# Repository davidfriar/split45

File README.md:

# The Split Forty Five

A small mechanical keyboard for those who cannot decide if they are ancient or modern.

* "Traditional" row-staggered layout
* Split for better ergonomics
* Based on the Nice!Nano controller for very low power consumption
* Uses Bluetooth Low Energy (BLE) both to connect each half and to connect to the computer

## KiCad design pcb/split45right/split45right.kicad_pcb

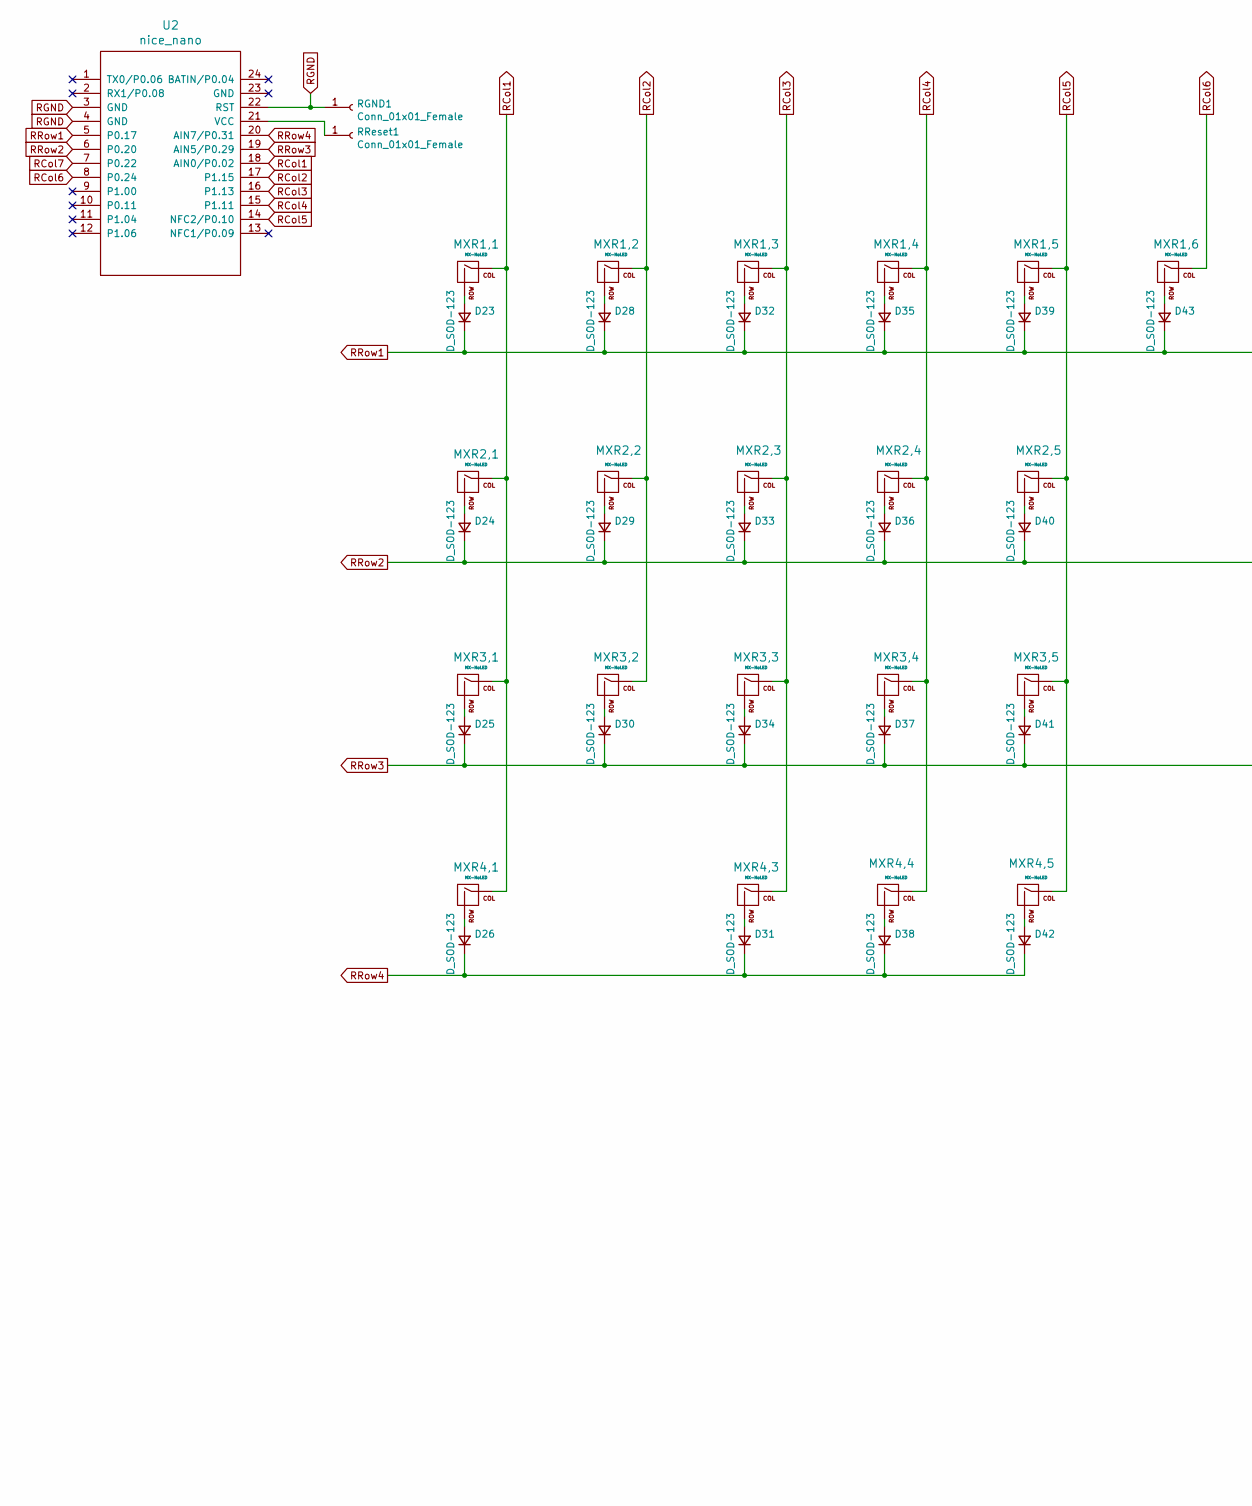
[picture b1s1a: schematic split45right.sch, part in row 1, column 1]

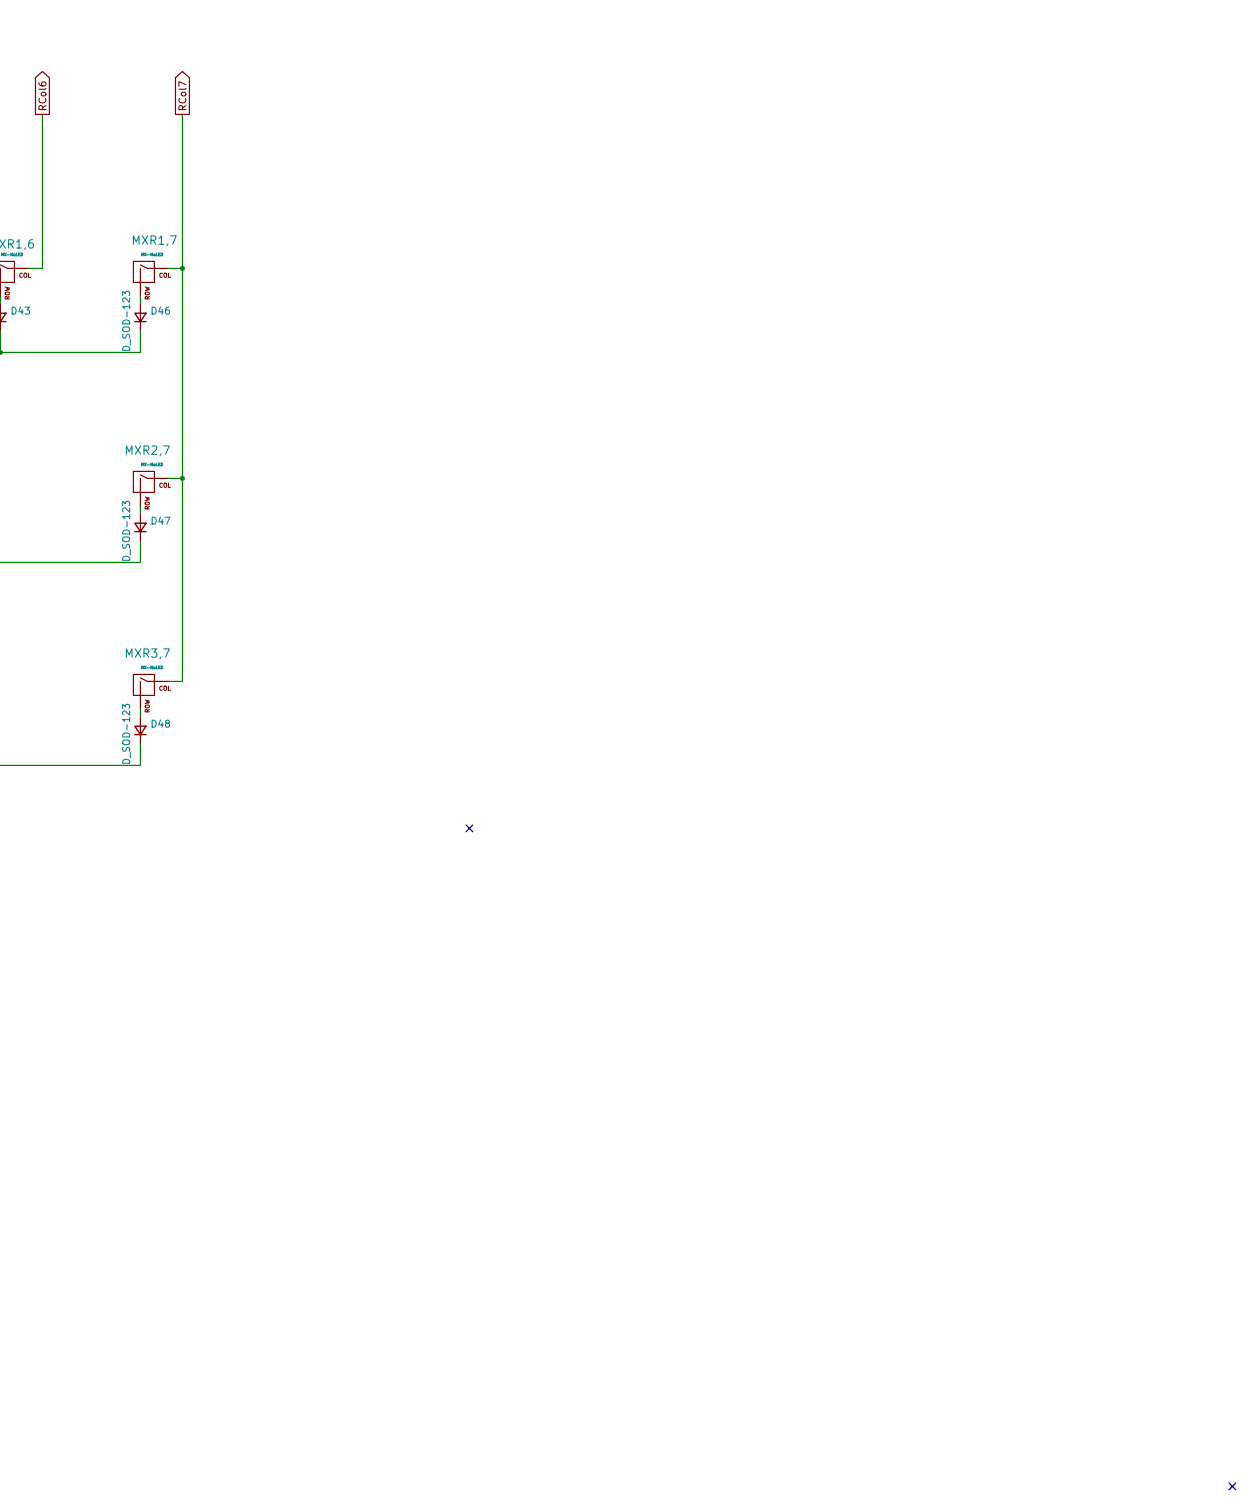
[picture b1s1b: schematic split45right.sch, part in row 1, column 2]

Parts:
D23, D24, D25, D26, D28, D29, D30, D31, D32, D33, D34, D35, D36, D37, D38, D39, D40, D41, D42, D43, D46, D47, D48: D_SOD-123
MXR1,1, MXR1,2, MXR1,3, MXR1,4, MXR1,5, MXR1,6, MXR1,7, MXR2,1, MXR2,2, MXR2,3, MXR2,4, MXR2,5, MXR3,1, MXR3,2, MXR3,3, MXR3,4, MXR3,5, MXR4,3, MXR4,5: MX-NoLED; MXOnly-1U-NoLED
MXR2,7: MX-NoLED; MXOnly-1.75U-NoLED
MXR3,7, MXR4,4: MX-NoLED; MXOnly-1.25U-NoLED
MXR4,1: MX-NoLED; MXOnly-2.75U-NoLED
RGND1: Conn_01x01_Female; SolderWire-0.15sqmm_1x01_D0.5mm_OD1.5mm
RReset1: Conn_01x01_Female; SolderWire-0.15sqmm_1x01_D0.5mm_OD1.5mm
U2: nice_nano

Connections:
unnamed: D23.2 (A), MXR1,1.2 (ROW)
unnamed: D24.2 (A), MXR2,1.2 (ROW)
unnamed: D25.2 (A), MXR3,1.2 (ROW)
unnamed: D26.2 (A), MXR4,1.2 (ROW)
unnamed: D28.2 (A), MXR1,2.2 (ROW)
unnamed: D29.2 (A), MXR2,2.2 (ROW)
unnamed: D30.2 (A), MXR3,2.2 (ROW)
unnamed: D31.2 (A), MXR4,3.2 (ROW)
unnamed: D32.2 (A), MXR1,3.2 (ROW)
unnamed: D33.2 (A), MXR2,3.2 (ROW)
unnamed: D34.2 (A), MXR3,3.2 (ROW)
unnamed: D35.2 (A), MXR1,4.2 (ROW)
unnamed: D36.2 (A), MXR2,4.2 (ROW)
unnamed: D37.2 (A), MXR3,4.2 (ROW)
unnamed: D38.2 (A), MXR4,4.2 (ROW)
unnamed: D39.2 (A), MXR1,5.2 (ROW)
unnamed: D40.2 (A), MXR2,5.2 (ROW)
unnamed: D41.2 (A), MXR3,5.2 (ROW)
unnamed: D42.2 (A), MXR4,5.2 (ROW)
unnamed: D43.2 (A), MXR1,6.2 (ROW)
unnamed: D46.2 (A), MXR1,7.2 (ROW)
unnamed: D47.2 (A), MXR2,7.2 (ROW)
unnamed: D48.2 (A), MXR3,7.2 (ROW)
unnamed: RReset1.1, U2.21 (VCC)
RCol1: MXR1,1.1 (COL), MXR2,1.1 (COL), MXR3,1.1 (COL), MXR4,1.1 (COL), U2.18 (AIN0/P0.02)
RCol2: MXR1,2.1 (COL), MXR2,2.1 (COL), MXR3,2.1 (COL), U2.17 (P1.15)
RCol3: MXR1,3.1 (COL), MXR2,3.1 (COL), MXR3,3.1 (COL), MXR4,3.1 (COL), U2.16 (P1.13)
RCol4: MXR1,4.1 (COL), MXR2,4.1 (COL), MXR3,4.1 (COL), MXR4,4.1 (COL), U2.15 (P1.11)
RCol5: MXR1,5.1 (COL), MXR2,5.1 (COL), MXR3,5.1 (COL), MXR4,5.1 (COL), U2.14 (NFC2/P0.10)
RCol6: MXR1,6.1 (COL), U2.8 (P0.24)
RCol7: MXR1,7.1 (COL), MXR2,7.1 (COL), MXR3,7.1 (COL), U2.7 (P0.22)
RGND: RGND1.1, U2.3 (GND), U2.4 (GND), U2.22 (RST)
RRow1: D23.1 (K), D28.1 (K), D32.1 (K), D35.1 (K), D39.1 (K), D43.1 (K), D46.1 (K), U2.5 (P0.17)
RRow2: D24.1 (K), D29.1 (K), D33.1 (K), D36.1 (K), D40.1 (K), D47.1 (K), U2.6 (P0.20)
RRow3: D25.1 (K), D30.1 (K), D34.1 (K), D37.1 (K), D41.1 (K), D48.1 (K), U2.19 (AIN5/P0.29)
RRow4: D26.1 (K), D31.1 (K), D38.1 (K), D42.1 (K), U2.20 (AIN7/P0.31)

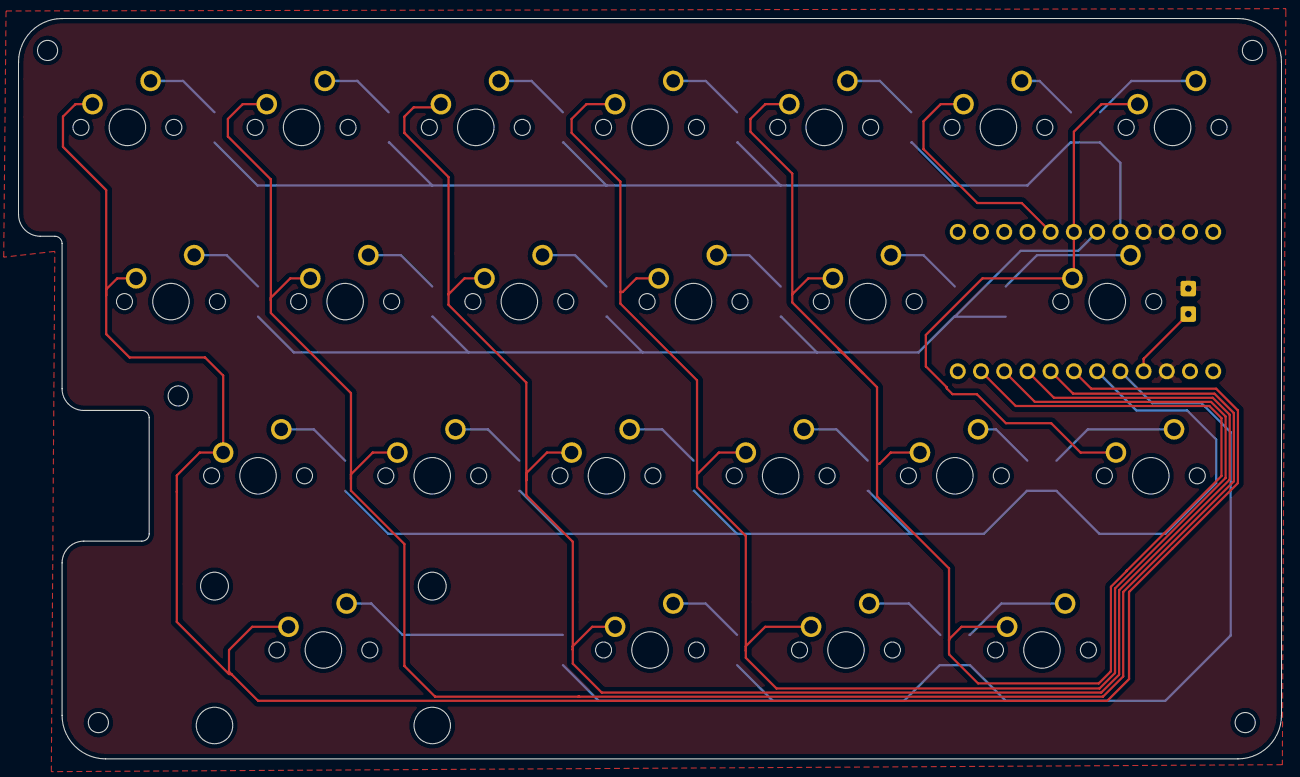
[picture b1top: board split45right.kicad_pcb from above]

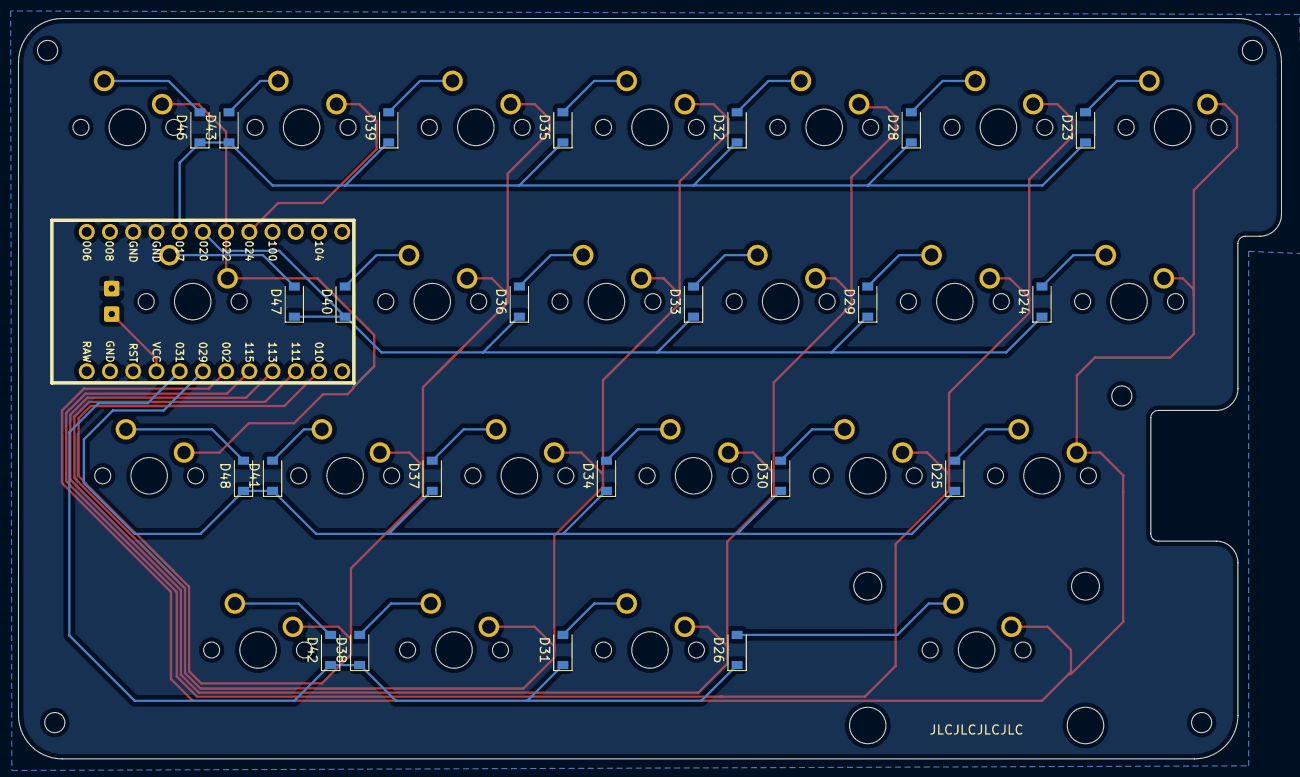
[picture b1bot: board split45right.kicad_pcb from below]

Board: 2 copper layers, 138.1 x 81.0 mm, 49 parts (23 on the bottom side), 36 nets.

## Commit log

2021-04-04 Add README
2021-04-04 Add kicad project
2021-04-04 Add libraries
2021-04-04 add gitignore
2021-04-04 add schema, pcb, place components
2021-04-05 route the left side
2021-04-05 right hand routing and fill areas
2021-04-05 add reset pads
2021-04-08 add pinouts and todo list
2021-04-09 move holes in base, add images and text to pcb
2021-04-09 remove submodule
2021-04-09 remove submodule directory
2021-04-09 add nice-nano-kicad files
2021-04-09 tweak position of boards on page
2021-04-09 add todo list
2021-04-09 split pcbs into separate projects
2021-04-10 add gerbers dir to .gitignore
2021-04-10 final changes for version 0.1
2021-04-10 update todo
2021-04-24 tiltable case
2021-05-05 case changes
2021-05-09 finish the case
2021-05-09 release case v0.1
